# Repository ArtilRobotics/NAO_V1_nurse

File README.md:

# NAO_V1_nurse
A sources files to repair the fingers and shoulders of NAO V1.

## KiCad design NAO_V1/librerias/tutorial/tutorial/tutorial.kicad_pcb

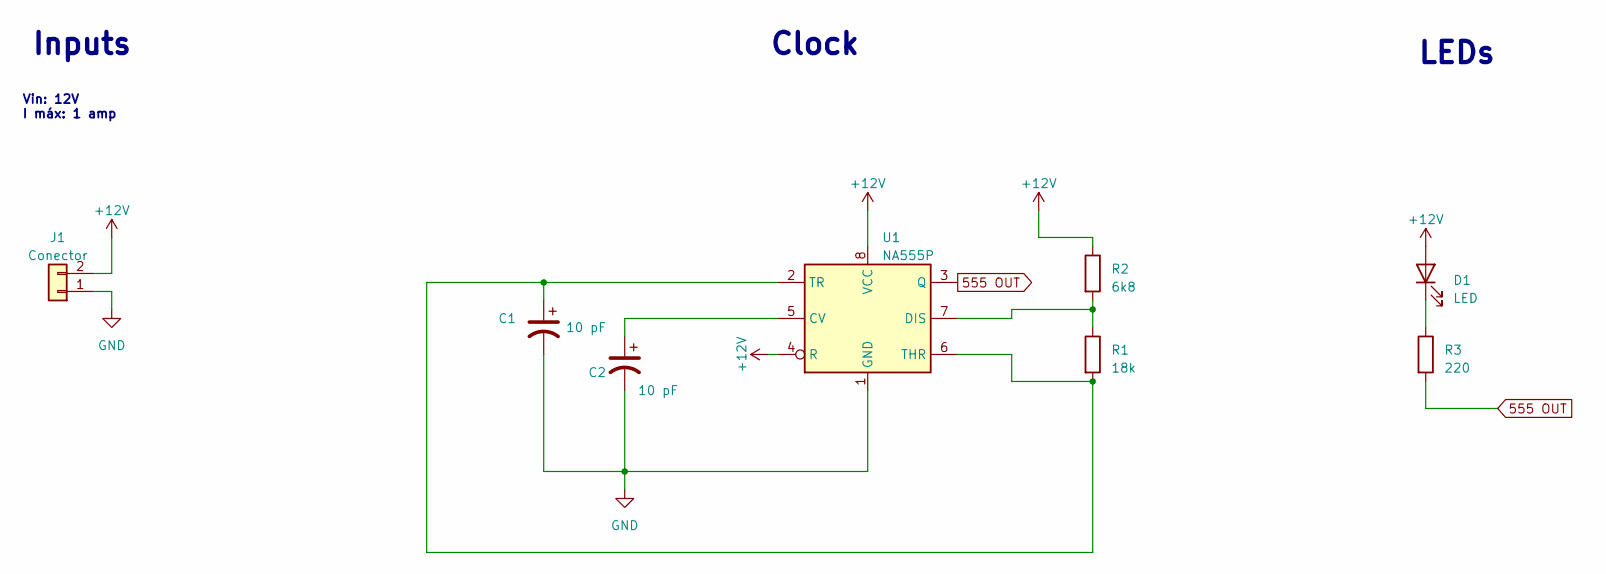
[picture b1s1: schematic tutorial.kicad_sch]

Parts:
C1, C2: 10 pF; CP_Radial_D10.0mm_P3.80mm
D1: LED; LED_D5.0mm_FlatTop
J1: Conector; TerminalBlock_bornier-2_P5.08mm
R1: 18k; R_1206_3216Metric
R2: 6k8; R_1206_3216Metric
R3: 220; R_1206_3216Metric
U1: NA555P; DIP-8_W7.62mm

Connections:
555 OUT: R3.2, U1.3 (Q)
+12V: D1.2 (A), J1.2, R2.1, U1.4 (R), U1.8 (VCC)
GND: C1.2, C2.2, J1.1, U1.1 (GND)
unnamed: D1.1 (K), R3.1
unnamed: C2.1, U1.5 (CV)
unnamed: R1.1, R2.2, U1.7 (DIS)
unnamed: C1.1, R1.2, U1.2 (TR), U1.6 (THR)

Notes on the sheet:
Clock
Inputs
Vin: 12V I máx: 1 amp
LEDs

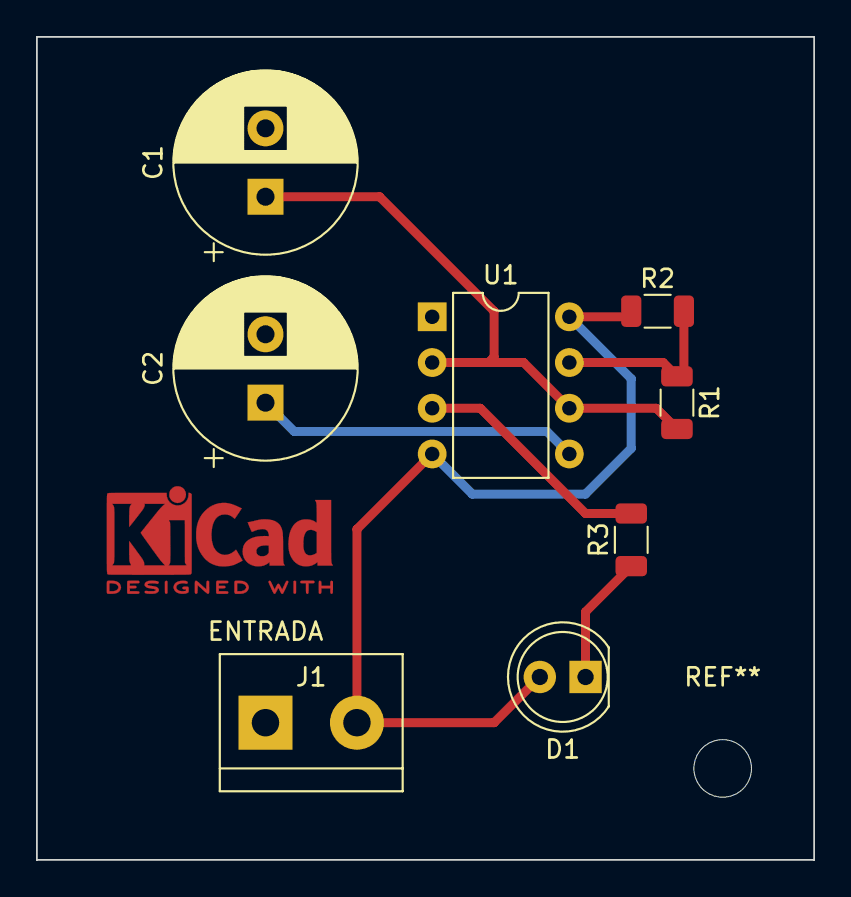
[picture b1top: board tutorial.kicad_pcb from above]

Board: 2 copper layers, 43.2 x 45.7 mm, 8 parts (0 on the bottom side), 7 nets.

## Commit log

2023-05-16 docs: NAO_V1 files
